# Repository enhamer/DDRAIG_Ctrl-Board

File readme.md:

<!---
#**============================================================================
#**
#**                    Ddraig Control Board
#**                  THIS REPOSITORY IS PART OF THE ENHAMER
#**
#** TITLE:           Ddraig Ctrl PCB (Circuit, Hardware)
#**
#** AUTHOR:          Marcin J. Kraśny
#**
#**					 Advanced Biological Imaging Laboratory
#**                  School of Physics
#**                  College of Science and Engineering
#**                  National University of Ireland, Galway
#**
#** SOURCE URL       https://github.com/enhamer/enhamer
#** COPYRIGHT        © 2015-2020 M.J.Kraśny
#** LICENSE          CERN-OHL-P v2
#** CREDITS          NEMESIS - Novel Energy Materials, Engineering Science 
#**                  and Integrated Systems
#**                  Department of Mechanical Engineering
#**					 University of Bath, UK
#**
#**============================================================================
#**============================================================================
-->

# DDRAIG - Control - Board
Part of:
**Energy Harvesting Measurement Rig (ENHAMER)**

*A System for Characterisation of Piezoelectric Materials and Associated Electronics for Vibration Powered Energy Harvesting Devices*

>For detailed **Information, Manuals and Description** please go to [**ENHAMER**](https://github.com/enhamer/enhamer/).

# Design software used
[EAGLE CAD](https://www.autodesk.com/products/eagle/overview)

## Ddraig Board Layout Top Side View

## Ddraig Board PCB

## Ddraig Board Assembled

# License
Copyright © 2015-2020 Marcin J. Kraśny

This work is licensed under the [CERN-OHL-P v2](LICENSE/cern_ohl_p_v2.txt); 
[CERN Open Hardware Licence version 2](https://cern.ch/cern-ohl).

You may redistribute and modify this documentation and make products
using it under the terms of the CERN-OHL-P v2 (<https:/cern.ch/cern-ohl>).
This documentation is distributed WITHOUT ANY EXPRESS OR IMPLIED WARRANTY INCLUDING OF MERCHANTABILITY, SATISFACTORY QUALITY AND FITNESS FOR A PARTICULAR PURPOSE. 
Please see the CERN-OHL-P v2 for applicable conditions.

# SOURCE
[https://github.com/enhamer](https://github.com/enhamer/enhamer/)

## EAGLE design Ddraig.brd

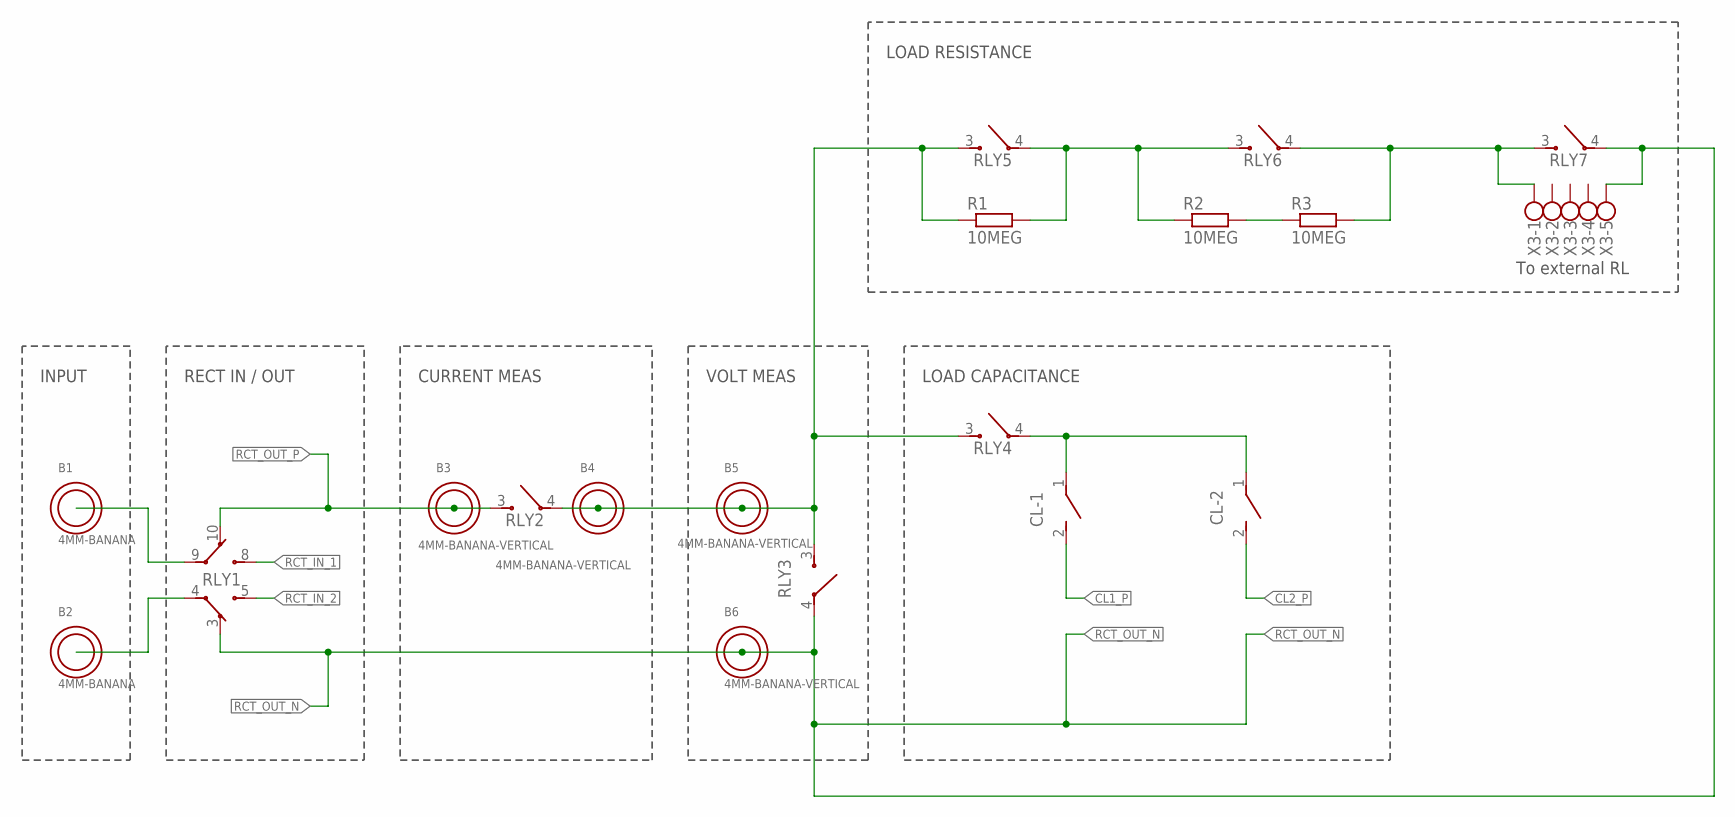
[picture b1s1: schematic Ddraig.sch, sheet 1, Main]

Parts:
B1, B2: 4MM-BANANA; 4MM-BANANA-VERTICAL
B3, B4, B5, B6: 4MM-BANANA-VERTICAL
CL-1, CL-2: DIP_SWITCH_01
R1, R2, R3: 10MEG; R2010
RLY1: AXICOM-V23079-D; AXICOM-V23079-SMT_MONO
RLY2, RLY3, RLY4, RLY5, RLY6, RLY7: OMRON-G5CA-1A-E; G5CA_MJK
X3: 5PIN_CONN_RAST3.5MM

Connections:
CL1_P: CL-1.2; also elsewhere on the board
CL2_P: CL-2.2; also elsewhere on the board
unnamed: B1.1, RLY1.9 (1)
unnamed: B2.1, RLY1.4
unnamed: B4.1, B5.1, R1.1, RLY2.4 (1), RLY3.3, RLY4.3, RLY5.3
unnamed: R3.2, RLY6.4 (1), RLY7.3, X3.1
unnamed: CL-1.1, CL-2.1, RLY4.4 (1)
unnamed: R1.2, R2.1, RLY5.4 (1), RLY6.3
unnamed: R2.2, R3.1
RCT_IN_1: RLY1.8 (3); also elsewhere on the board
RCT_IN_2: RLY1.5 (6); also elsewhere on the board
RCT_OUT_N: B6.1, RLY1.3 (5), RLY3.4 (1), RLY7.4 (1), X3.5; also elsewhere on the board
RCT_OUT_P: B3.1, RLY1.10 (2), RLY2.3; also elsewhere on the board

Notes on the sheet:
CURRENT MEAS
VOLT MEAS
LOAD CAPACITANCE
LOAD RESISTANCE
INPUT
RECT IN / OUT
To external RL

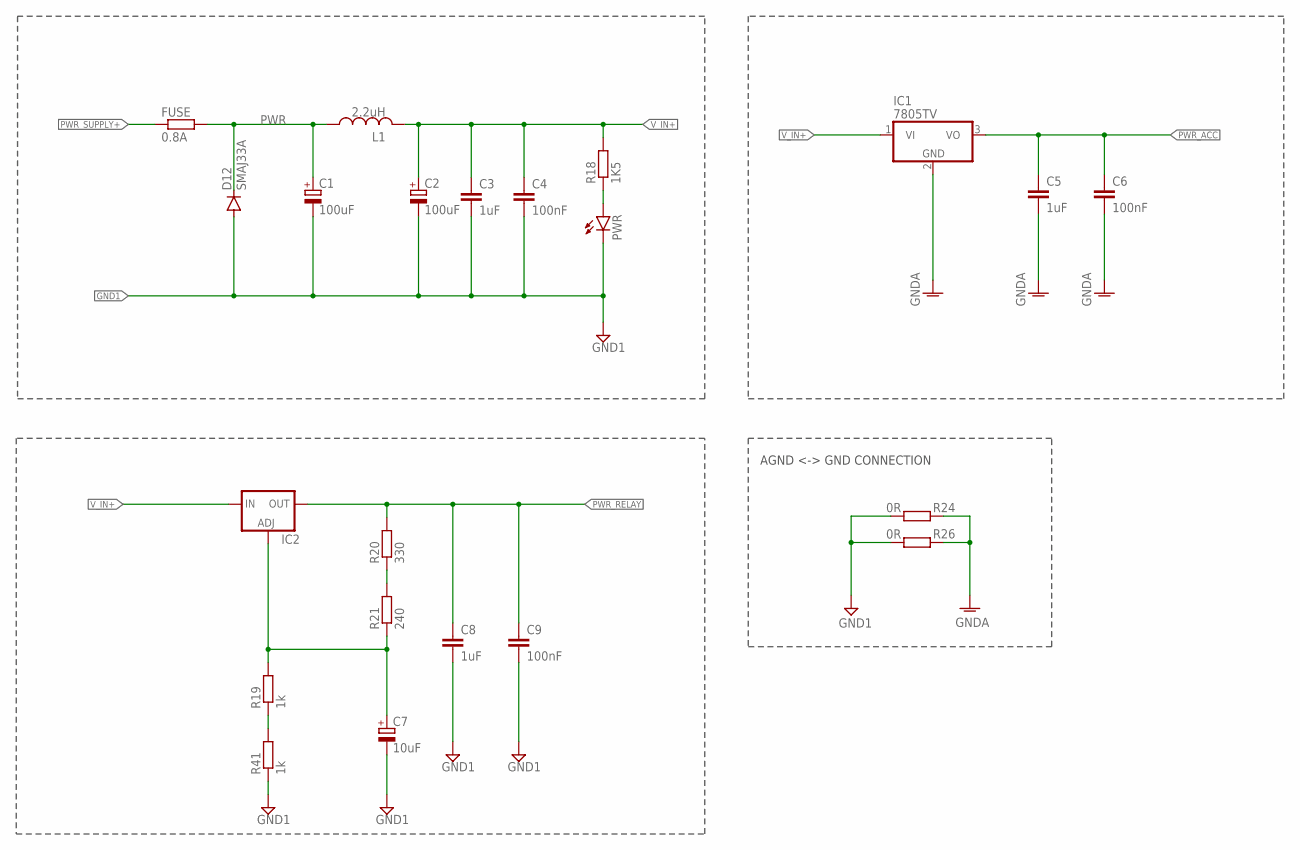
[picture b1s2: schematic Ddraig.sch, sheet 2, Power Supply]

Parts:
C1, C2: 100uF; PANASONIC-CAPAE660X800N
C3, C5, C8: 1uF; C0805
C4, C6, C9: 100nF; C0805
C7: 10uF; PANASONIC-CAPAE660X800N
D12: SMAJ33A; DO-214AC
FUSE: 0.8A; 1206
IC1: 7805TV; TO220V
IC2: LM317TS; 317TS
L1: 2.2uH; 0805
PWR: LEDSMT1206; 1206
R18: 1K5; R0805
R19, R41: 1k; R0805
R20: 330; R0805
R21: 240; R0805
R24, R26: 0R; R0805

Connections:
GND1: C1.2 (-), C2.2 (-), C3.2, C4.2, C7.2 (-), C8.2, C9.2, D12.A, PWR.C, R24.2, R26.2, R41.1; also elsewhere on the board
GNDA: C5.2, C6.2, IC1.2 (GND), R24.1, R26.1; also elsewhere on the board
unnamed: PWR.A, R18.1
unnamed: C7.1 (+), IC2.1 (ADJ), R19.2, R21.1
unnamed: R20.1, R21.2
unnamed: R19.1, R41.2
PWR: C1.1 (+), D12.C, FUSE.2, L1.1
PWR_ACC: C5.1, C6.1, IC1.3 (VO); also elsewhere on the board
PWR_RELAY: C8.1, C9.1, IC2.2 (OUT), R20.2; also elsewhere on the board
PWR_SUPPLY+: FUSE.1; also elsewhere on the board
V_IN+: C2.1 (+), C3.1, C4.1, IC1.1 (VI), IC2.3 (IN), L1.2, R18.2

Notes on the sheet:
AGND <-> GND CONNECTION

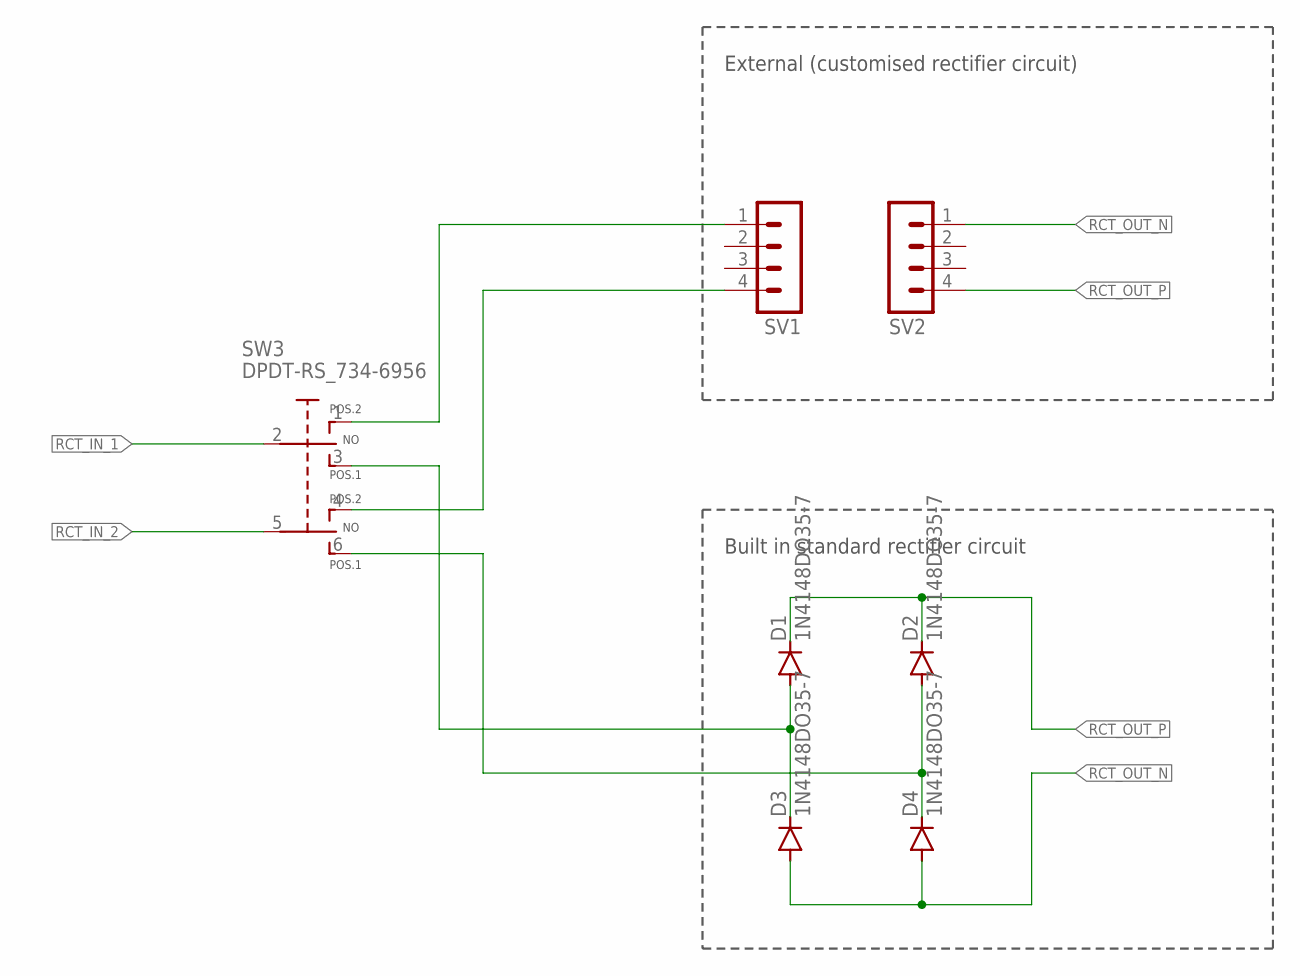
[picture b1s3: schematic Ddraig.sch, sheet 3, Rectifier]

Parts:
D1, D2, D3, D4: 1N4148DO35-7; DO35-7
SV1, SV2: MA04-1
SW3: DPDT-RS_734-6956

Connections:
unnamed: SV1.1, SW3.1
unnamed: SV1.4, SW3.4
unnamed: D1.A, D3.C, SW3.3
unnamed: D2.A, D4.C, SW3.6
RCT_IN_1: SW3.2; also elsewhere on the board
RCT_IN_2: SW3.5; also elsewhere on the board
RCT_OUT_N: D3.A, D4.A, SV2.1; also elsewhere on the board
RCT_OUT_P: D1.C, D2.C, SV2.4; also elsewhere on the board

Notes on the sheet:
External (customised rectifier circuit)
Built in standard rectifier circuit

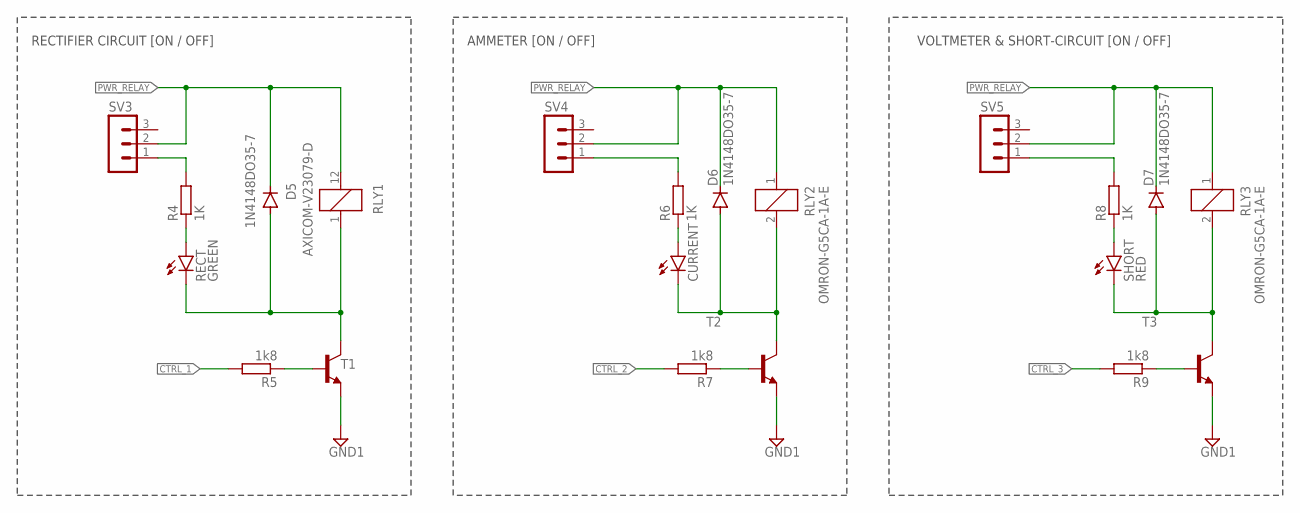
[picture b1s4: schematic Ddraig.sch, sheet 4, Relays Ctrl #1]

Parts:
CURRENT: LEDSMT1206; 1206
D5, D6, D7: 1N4148DO35-7; DO35-7
R4, R6, R8: 1K; R0805
R5, R7, R9: 1k8; R0805
RECT: GREEN; 1206
RLY1: AXICOM-V23079-D; AXICOM-V23079-SMT_MONO
RLY2, RLY3: OMRON-G5CA-1A-E; G5CA_MJK
SHORT: RED; 1206
SV3, SV4, SV5: MA03-1
T1, T2, T3: BC337-25-NPN-TO92-CBE; TO92-CBE

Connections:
CTRL_1: R5.2; also elsewhere on the board
CTRL_2: R7.2; also elsewhere on the board
CTRL_3: R9.2; also elsewhere on the board
GND1: T1.E, T2.E, T3.E; also elsewhere on the board
unnamed: R4.2, SV3.1
unnamed: R4.1, RECT.A
unnamed: D5.A, RECT.C, RLY1.1, T1.C
unnamed: CURRENT.A, R6.1
unnamed: CURRENT.C, D6.A, RLY2.2, T2.C
unnamed: R5.1, T1.B
unnamed: R6.2, SV4.1
unnamed: R7.1, T2.B
unnamed: R8.1, SHORT.A
unnamed: D7.A, RLY3.2, SHORT.C, T3.C
unnamed: R8.2, SV5.1
unnamed: R9.1, T3.B
PWR_RELAY: D5.C, D6.C, D7.C, RLY1.12 (2), RLY2.1, RLY3.1, SV3.2, SV4.2, SV5.2; also elsewhere on the board

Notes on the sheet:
RECTIFIER CIRCUIT [ON / OFF]
AMMETER [ON / OFF]
VOLTMETER & SHORT-CIRCUIT [ON / OFF]

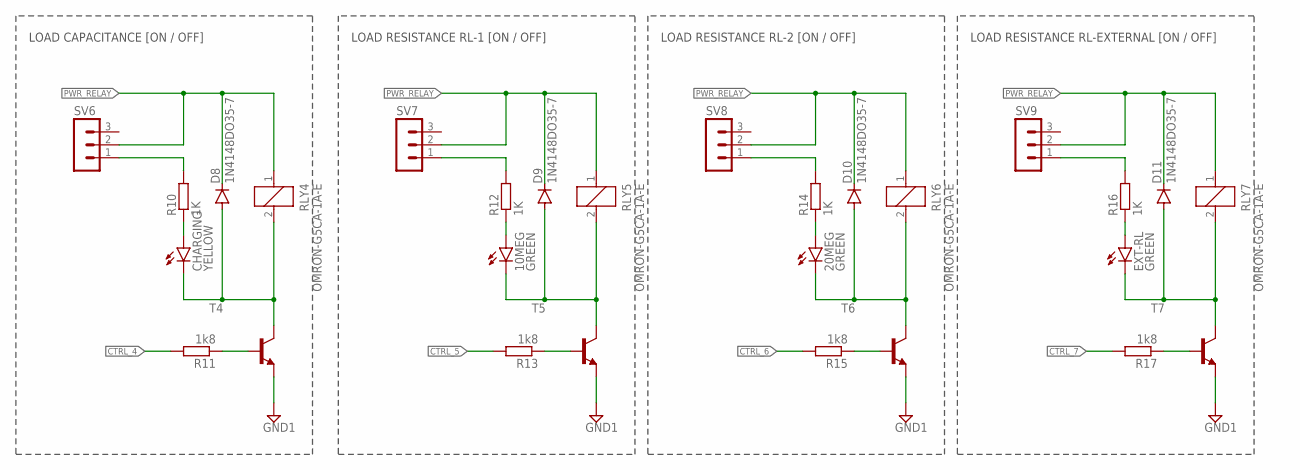
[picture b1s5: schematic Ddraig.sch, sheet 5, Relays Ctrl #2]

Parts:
10MEG, 20MEG: GREEN; 1206
CHARGING: YELLOW; 1206
D8, D9, D10, D11: 1N4148DO35-7; DO35-7
EXT-RL: GREEN; 1206
R10, R12, R14, R16: 1K; R0805
R11, R13, R15, R17: 1k8; R0805
RLY4, RLY5, RLY6, RLY7: OMRON-G5CA-1A-E; G5CA_MJK
SV6, SV7, SV8, SV9: MA03-1
T4, T5, T6, T7: BC337-25-NPN-TO92-CBE; TO92-CBE

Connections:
CTRL_4: R11.2; also elsewhere on the board
CTRL_5: R13.2; also elsewhere on the board
CTRL_6: R15.2; also elsewhere on the board
CTRL_7: R17.2; also elsewhere on the board
GND1: T4.E, T5.E, T6.E, T7.E; also elsewhere on the board
unnamed: CHARGING.A, R10.1
unnamed: CHARGING.C, D8.A, RLY4.2, T4.C
unnamed: R10.2, SV6.1
unnamed: R11.1, T4.B
unnamed: 10MEG.A, R12.1
unnamed: 10MEG.C, D9.A, RLY5.2, T5.C
unnamed: R12.2, SV7.1
unnamed: R13.1, T5.B
unnamed: 20MEG.A, R14.1
unnamed: 20MEG.C, D10.A, RLY6.2, T6.C
unnamed: R14.2, SV8.1
unnamed: R15.1, T6.B
unnamed: EXT-RL.A, R16.1
unnamed: D11.A, EXT-RL.C, RLY7.2, T7.C
unnamed: R16.2, SV9.1
unnamed: R17.1, T7.B
PWR_RELAY: D8.C, D9.C, D10.C, D11.C, RLY4.1, RLY5.1, RLY6.1, RLY7.1, SV6.2, SV7.2, SV8.2, SV9.2; also elsewhere on the board

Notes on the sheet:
LOAD CAPACITANCE [ON / OFF]
LOAD RESISTANCE RL-1 [ON / OFF]
LOAD RESISTANCE RL-2 [ON / OFF]
LOAD RESISTANCE RL-EXTERNAL [ON / OFF]

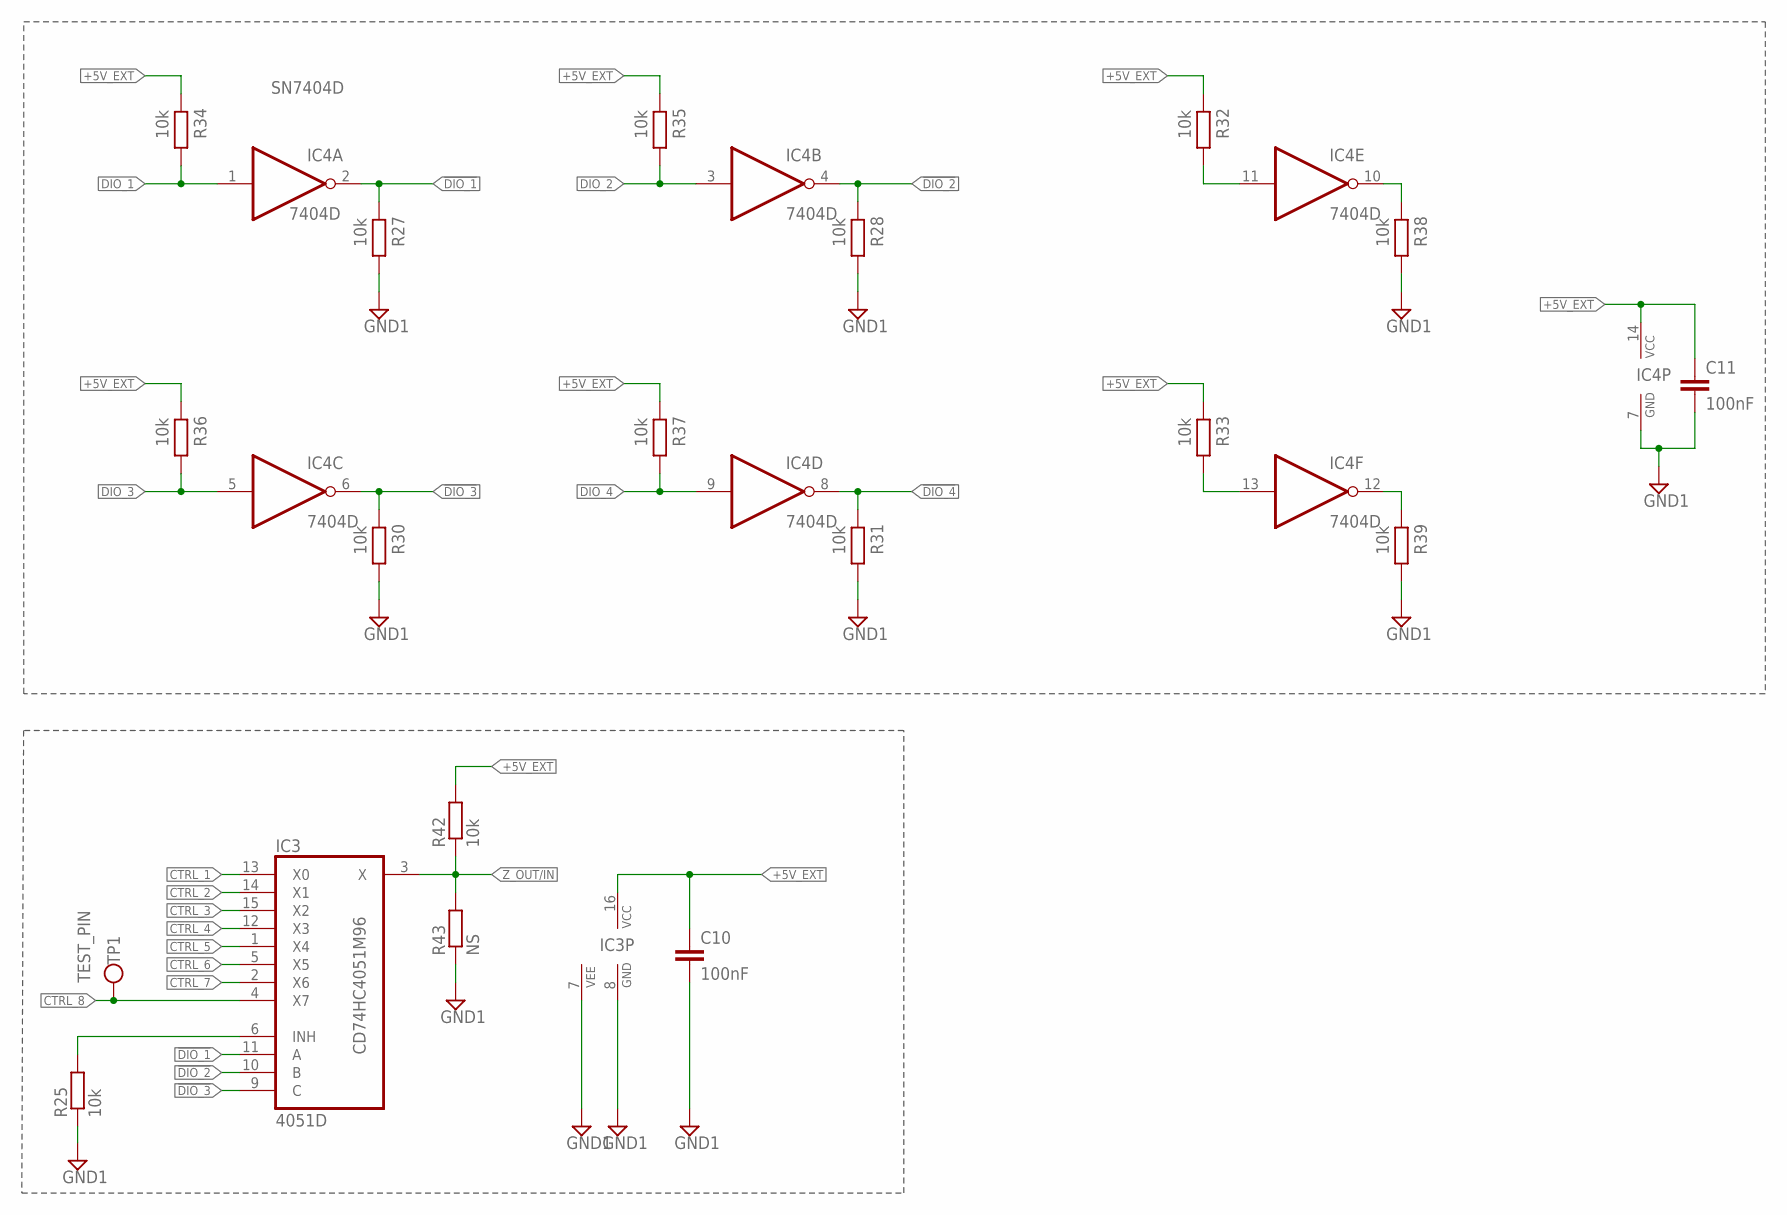
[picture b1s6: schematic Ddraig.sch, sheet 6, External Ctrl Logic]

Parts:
C10, C11: 100nF; C0805
IC3: 4051D; SO16
IC4: 7404D; SO14
R25, R27, R28, R30, R31, R32, R33, R34, R35, R36, R37, R38, R39, R42: 10k; R0805
R43: NS; R0805
TP1: TEST_PIN; 1-TEST_PIN

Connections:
!DIO_1: IC3.11 (A), IC4.2 (O), R27.2
!DIO_2: IC3.10 (B), IC4.4 (O), R28.2
!DIO_3: IC3.9 (C), IC4.6 (O), R30.2
!DIO_4: IC4.8 (O), R31.2
+5V_EXT: C10.1, C11.1, IC3.16 (VCC), IC4.14 (VCC), R32.2, R33.2, R34.2, R35.2, R36.2, R37.2, R42.2; also elsewhere on the board
CTRL_1: IC3.13 (X0); also elsewhere on the board
CTRL_2: IC3.14 (X1); also elsewhere on the board
CTRL_3: IC3.15 (X2); also elsewhere on the board
CTRL_4: IC3.12 (X3); also elsewhere on the board
CTRL_5: IC3.1 (X4); also elsewhere on the board
CTRL_6: IC3.5 (X5); also elsewhere on the board
CTRL_7: IC3.2 (X6); also elsewhere on the board
CTRL_8: IC3.4 (X7), TP1.1
DIO_1: IC4.1 (I), R34.1; also elsewhere on the board
DIO_2: IC4.3 (I), R35.1; also elsewhere on the board
DIO_3: IC4.5 (I), R36.1; also elsewhere on the board
DIO_4: IC4.9 (I), R37.1; also elsewhere on the board
GND1: C10.2, C11.2, IC3.7 (VEE), IC3.8 (GND), IC4.7 (GND), R25.1, R27.1, R28.1, R30.1, R31.1, R38.1, R39.1, R43.1; also elsewhere on the board
unnamed: IC4.11 (I), R32.1
unnamed: IC3.6 (INH), R25.2
unnamed: IC4.13 (I), R33.1
unnamed: IC4.10 (O), R38.2
unnamed: IC4.12 (O), R39.2
Z_OUT/IN: IC3.3 (X), R42.1, R43.2

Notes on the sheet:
CD74HC4051M96
SN7404D

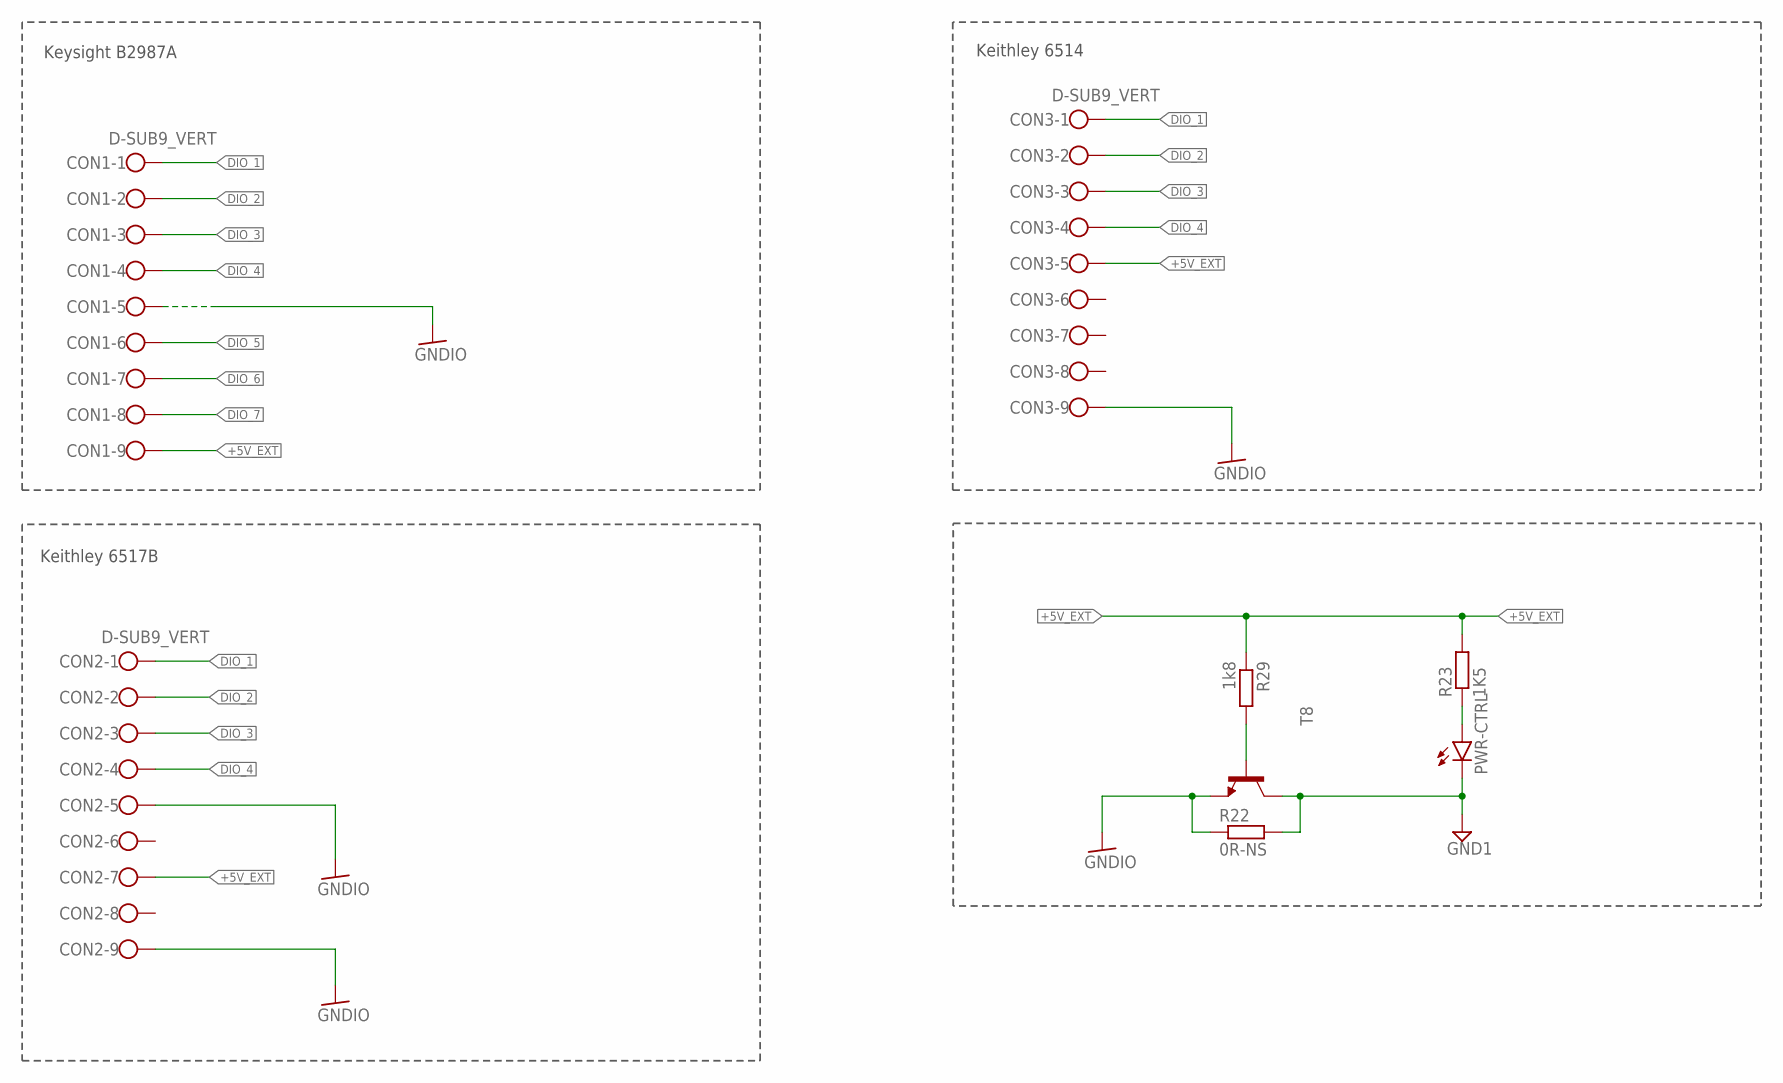
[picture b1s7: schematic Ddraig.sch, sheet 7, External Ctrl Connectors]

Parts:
CON1, CON2, CON3: D-SUB9_VERT; D-SUB9-VERTICAL
PWR-CTRL: LEDSMT1206; 1206
R22: 0R-NS; R0805
R23: 1K5; R0805
R29: 1k8; R0805
T8: BC337-25-NPN-TO92-CBE; TO92-CBE

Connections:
+5V_EXT: CON1.9, CON2.7, CON3.5, R23.2, R29.1; also elsewhere on the board
DIO_1: CON1.1, CON2.1, CON3.1; also elsewhere on the board
DIO_2: CON1.2, CON2.2, CON3.2; also elsewhere on the board
DIO_3: CON1.3, CON2.3, CON3.3; also elsewhere on the board
DIO_4: CON1.4, CON2.4, CON3.4; also elsewhere on the board
DIO_5: CON1.6
DIO_6: CON1.7
DIO_7: CON1.8
GND1: PWR-CTRL.C, R22.2, T8.C; also elsewhere on the board
GNDIO: CON1.5, CON2.5, CON2.9, CON3.9, R22.1, T8.E
unnamed: PWR-CTRL.A, R23.1
unnamed: R29.2, T8.B

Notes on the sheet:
Keysight B2987A
Keithley 6517B
Keithley 6514

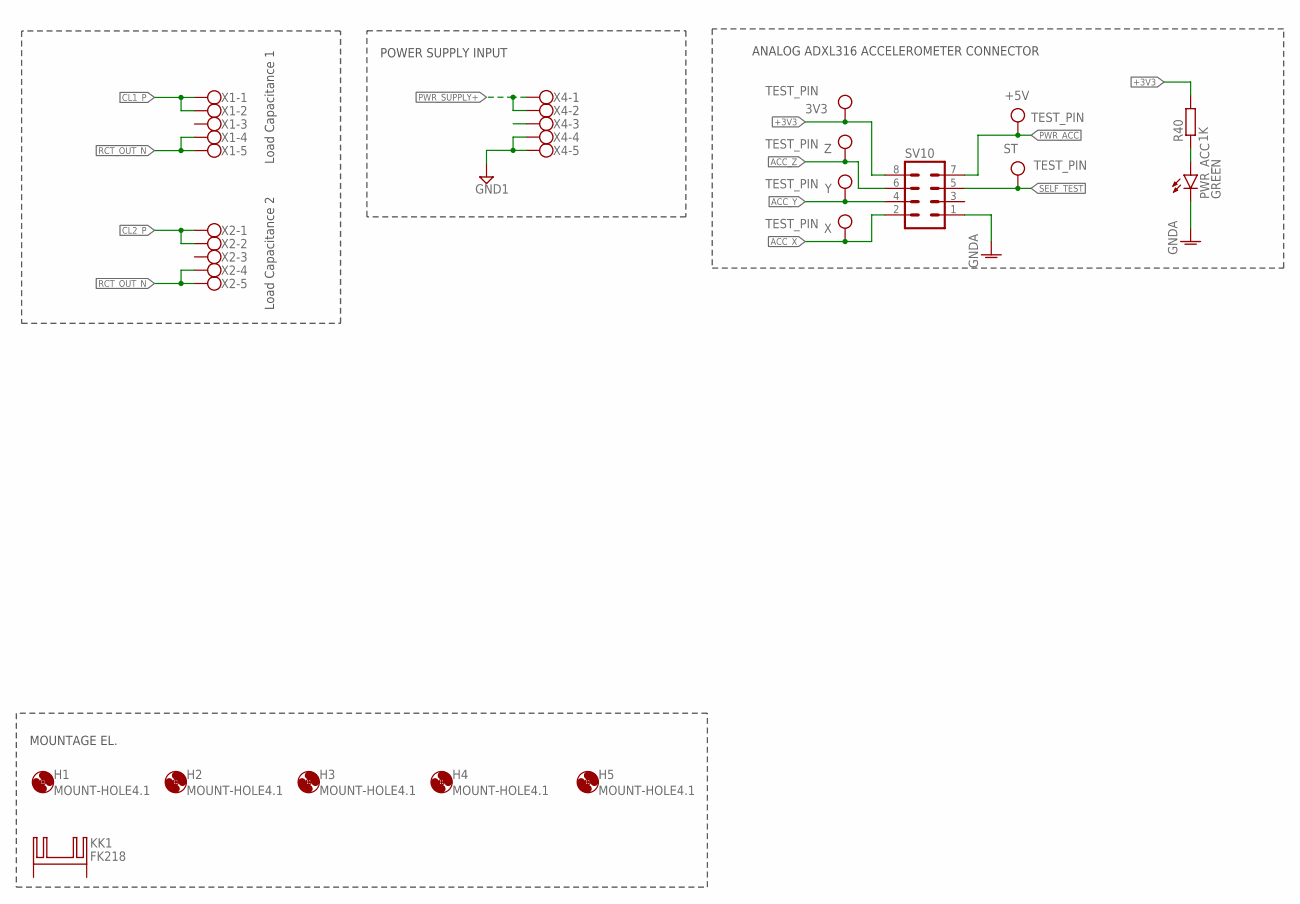
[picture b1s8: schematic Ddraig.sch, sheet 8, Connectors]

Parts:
3V3: TEST_PIN; 1-TEST_PIN
+5V: TEST_PIN; 1-TEST_PIN
H1, H2, H3, H4, H5: MOUNT-HOLE4.1; 4,1
KK1: FK218
PWR_ACC: GREEN; 1206
R40: 1K; R0805
ST: TEST_PIN; 1-TEST_PIN
SV10: MA04-2
X: TEST_PIN; 1-TEST_PIN
X1, X2, X4: 5PIN_CONN_RAST3.5MM
Y: TEST_PIN; 1-TEST_PIN
Z: TEST_PIN; 1-TEST_PIN

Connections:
+3V3: 3V3.1, R40.2, SV10.8
ACC_X: SV10.2, X.1
ACC_Y: SV10.4, Y.1
ACC_Z: SV10.6, Z.1
CL1_P: X1.1, X1.2; also elsewhere on the board
CL2_P: X2.1, X2.2; also elsewhere on the board
GND1: X4.4, X4.5; also elsewhere on the board
GNDA: PWR_ACC.C, SV10.1; also elsewhere on the board
unnamed: PWR_ACC.A, R40.1
PWR_ACC: +5V.1, SV10.7; also elsewhere on the board
PWR_SUPPLY+: X4.1, X4.2; also elsewhere on the board
RCT_OUT_N: X1.4, X1.5, X2.4, X2.5; also elsewhere on the board
SELF_TEST: ST.1, SV10.5

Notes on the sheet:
Load Capacitance 1
Load Capacitance 2
MOUNTAGE EL.
ANALOG ADXL316 ACCELEROMETER CONNECTOR
POWER SUPPLY INPUT

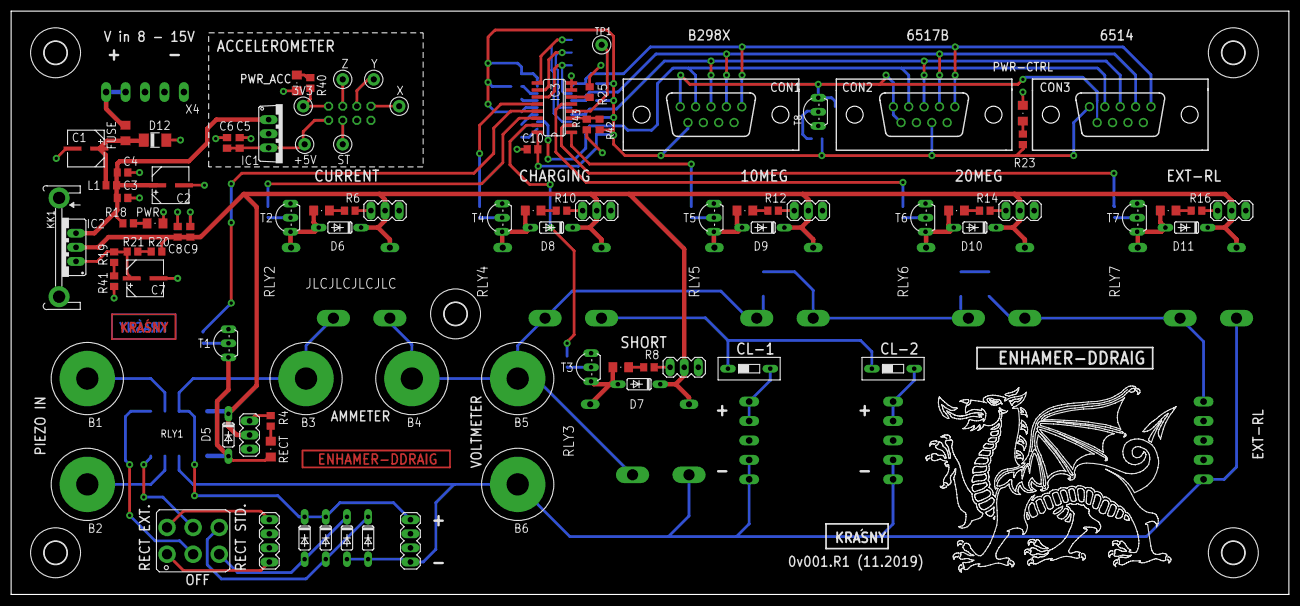
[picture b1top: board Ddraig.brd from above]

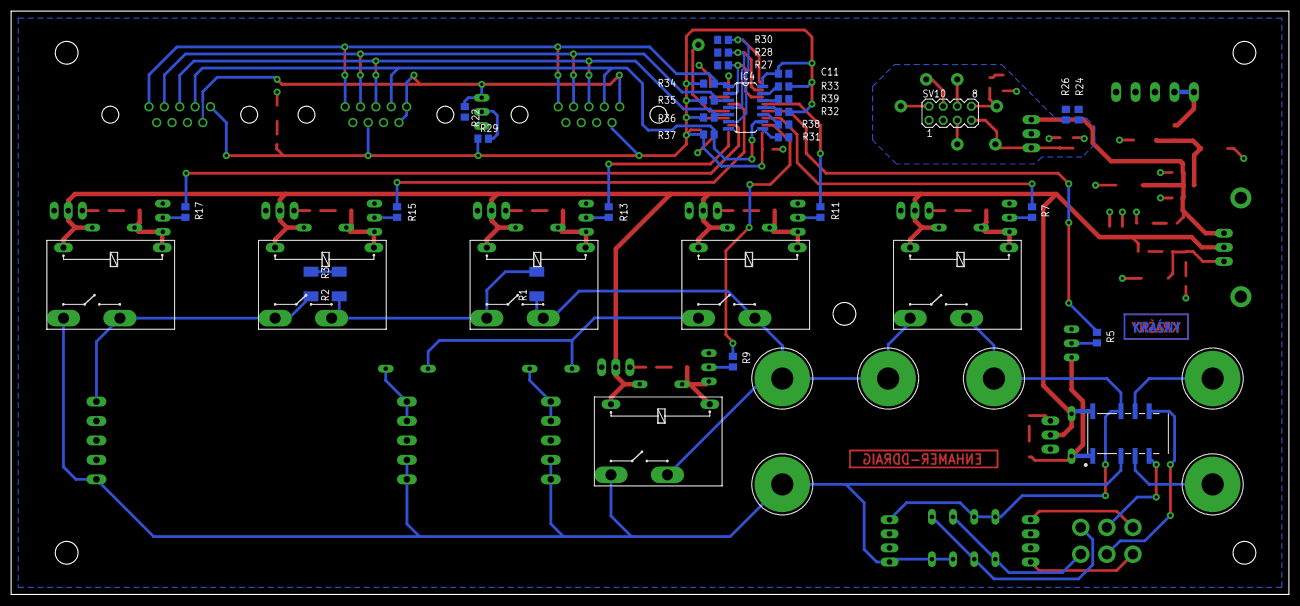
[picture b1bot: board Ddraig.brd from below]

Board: 2 copper layers, 230.0 x 105.0 mm, 136 parts (30 on the bottom side), 88 nets.

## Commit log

2020-05-10 Ddraig - initial commit
2020-06-03 License and repo readme file update
